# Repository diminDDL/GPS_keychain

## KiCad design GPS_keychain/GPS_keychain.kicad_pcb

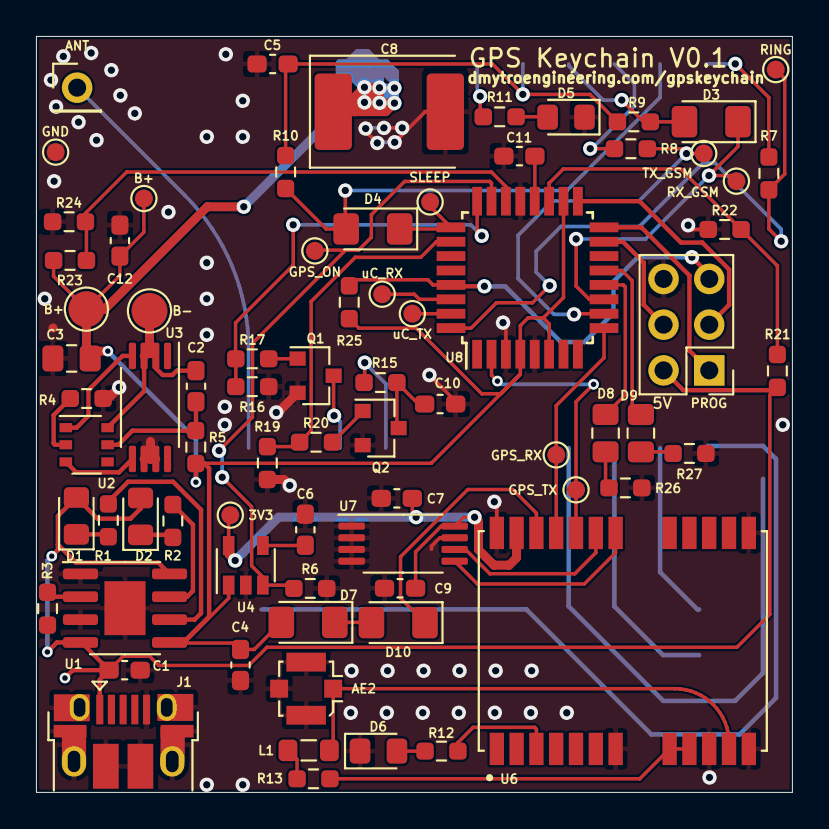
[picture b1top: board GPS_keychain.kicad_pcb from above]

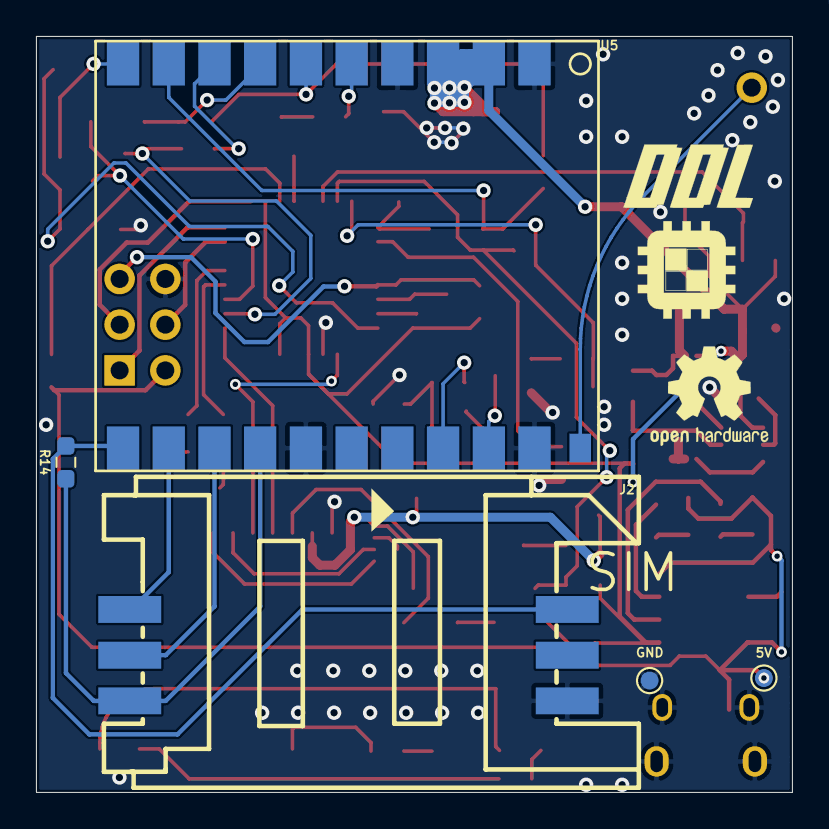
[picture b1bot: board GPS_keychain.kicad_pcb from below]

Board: 2 copper layers, 42.0 x 42.0 mm, 80 parts (5 on the bottom side), 63 nets.

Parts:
3V3: 3V3; TestPoint_Pad_D1.0mm
5V: 5V; TestPoint_Pad_D1.0mm
AE2: Antenna_Shield; U.FL_Molex_MCRF_73412-0110_Vertical
ANT: ANT; PinHeader_1x01_P2.54mm_Vertical
B+: BAT+; TestPoint_Pad_D1.0mm
B+#2: B+; TestPoint_Pad_D2.0mm
B-: B-; TestPoint_Pad_D2.0mm
C1, C2: 100n; C_0603_1608Metric_Pad1.08x0.95mm_HandSolder
C3: 10uF; C_0805_2012Metric_Pad1.18x1.45mm_HandSolder
C4, C7: 1uF; C_0603_1608Metric_Pad1.08x0.95mm_HandSolder
C5, C9, C10, C11, C12: 0.1uF; C_0603_1608Metric_Pad1.08x0.95mm_HandSolder
C6: 22nF; C_0603_1608Metric_Pad1.08x0.95mm_HandSolder
C8: 100uF; CP_EIA-7360-38_Kemet-E
D1: LED_G; LED_0805_2012Metric_Pad1.15x1.40mm_HandSolder
D2: LED_R; LED_0805_2012Metric_Pad1.15x1.40mm_HandSolder
D3, D4, D7, D10: S1MF; D_1206_3216Metric_Pad1.42x1.75mm_HandSolder
D5, D6: LED; LED_0805_2012Metric_Pad1.15x1.40mm_HandSolder
D8: LED_Y; C_0805_2012Metric_Pad1.18x1.45mm_HandSolder
D9: LED_B; C_0805_2012Metric_Pad1.18x1.45mm_HandSolder
GND: GND; TestPoint_Pad_D1.0mm
GND#2: GND; TestPoint_Pad_D1.0mm
GPS_ON: GPS_ON; TestPoint_Pad_D1.0mm
GPS_RX: RX_GPS; TestPoint_Pad_D1.0mm
GPS_TX: TX_GPS; TestPoint_Pad_D1.0mm
J1: USB_B_Micro; USB_Micro-B_Amphenol_10103594-0001LF_Horizontal
J2: SIM; SIM-SMD_XKSIM-011B-P6
L1: 27uH; L_0805_2012Metric_Pad1.05x1.20mm_HandSolder
PROG: AVR-ISP-6; PinHeader_2x03_P2.54mm_Vertical
Q1, Q2: BC846; SOT-23
R1, R2, R26, R27: 1K; R_0603_1608Metric_Pad0.98x0.95mm_HandSolder
R3: 1.2k; R_0603_1608Metric_Pad0.98x0.95mm_HandSolder
R4, R11, R12, R15: 1k; R_0603_1608Metric_Pad0.98x0.95mm_HandSolder
R5: 100; R_0603_1608Metric_Pad0.98x0.95mm_HandSolder
R6, R9, R10, R14, R17, R20, R21, R22, R25: 10k; R_0603_1608Metric_Pad0.98x0.95mm_HandSolder
R7, R8: 200; R_0603_1608Metric_Pad0.98x0.95mm_HandSolder
R13: 22R; R_0603_1608Metric_Pad0.98x0.95mm_HandSolder
R16, R19: 47k; R_0603_1608Metric_Pad0.98x0.95mm_HandSolder
R23: 10M; R_0603_1608Metric_Pad0.98x0.95mm_HandSolder
R24: 350k; R_0603_1608Metric_Pad0.98x0.95mm_HandSolder
RING: RG_GSM; TestPoint_Pad_D1.0mm
RX_GSM: RX_GSM; TestPoint_Pad_D1.0mm
SLEEP: SL_GSM; TestPoint_Pad_D1.0mm
TX_GSM: TX_GSM; TestPoint_Pad_D1.0mm
U1: TP4056; SOIC-8-1EP_3.9x4.9mm_P1.27mm_EP2.29x3mm
U2: DW01; TSOP-6_1.65x3.05mm_P0.95mm
U3: FS8205A; TSSOP-8_4.4x3mm_P0.65mm
U4: RT9193-33GB; SOT-23-5
U5: NeowayM590
U6: NEO-6M-GPS; XCVR_NEO-6M-GPS
U7: 24LC32; TSSOP-8_4.4x3mm_P0.65mm
U8: ATmega328P-AU; TQFP-32_7x7mm_P0.8mm
uC_RX: RX_uC; TestPoint_Pad_D1.0mm
uC_TX: TX_uC; TestPoint_Pad_D1.0mm

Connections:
+3V3: 3V3.1, C7.1, C9.2, U4.5, U6.23, U7.8
+5V: 5V.1, C1.1, D1.2, D2.2, J1.1, PROG.2, R21.2, U1.4, U1.8
+BATT: B+.1, B+#2.1, C3.1, C4.1, C8.1, C12.2, D7.2, R5.2, R23.2, R25.1, U1.5, U4.1, U5.2, U5.3, U8.4, U8.6, U8.18
/5V_sense: R21.1, R22.2, U8.19
/BAT_sense: R23.1, R24.2, U8.22
/GPS_ON: GPS_ON.1, R6.2, U4.3, U8.23
/GSM_EMOFF: R19.1, R20.1, U8.26
/GSM_EN: R16.1, R17.1, U8.24
/RING: R7.2, RING.1, U8.32
/RXD1: GPS_RX.1, U6.21, U8.9
/RXD2: D3.1, RX_GSM.1, U8.11
/RXD_uC: U8.30, uC_RX.1
/SLEEP: D4.1, SLEEP.1, U8.25
/TXD1: GPS_TX.1, U6.20, U8.2
/TXD2: R8.2, TX_GSM.1, U8.10
/TXD_uC: U8.31, uC_TX.1
GND: AE2.2, C1.2, C3.2, C4.2, C5.1, C6.2, C7.2, C8.2, C9.1, C10.2, C11.1, C12.1, D5.1, D6.1, GND.1, GND#2.1, J1.5, J1.6, J2.4, PROG.6, Q1.2, Q2.2, R3.1, R4.1, R6.1, R16.2, R19.2, R22.1, R24.1, R26.2, R27.1, U1.1, U1.3, U1.9, U3.6, U3.7, U4.2, U5.1, U5.4, U5.15, U5.20, U6.7, U6.10, U6.12, U6.13, U6.24, U7.1, U7.2, U7.3, U7.4, U7.7, U8.3, U8.5, U8.21
unnamed: ANT.1, U5.21
unnamed: AE2.1, L1.2, U6.11
unnamed: C2.1, R5.1, U2.5
unnamed: B-.1, C2.2, U2.6, U3.2, U3.3
unnamed: C5.2, R9.1, R10.1, U5.6
unnamed: C6.1, U4.4
unnamed: C10.1, Q2.3, R15.1
unnamed: C11.2, U8.20
unnamed: D1.1, R1.2
unnamed: D2.1, R2.2
unnamed: D3.2, R9.2, U5.7
unnamed: D4.2, R10.2, U5.9
unnamed: D5.2, R11.2
unnamed: D6.2, R12.1
unnamed: D8.1, R26.1
unnamed: D8.2, U8.12
unnamed: D9.1, R27.2
unnamed: D9.2, U8.13
unnamed: D10.1, U6.22
unnamed: D7.1, D10.2
unnamed: J2.1, R14.1, U5.14
unnamed: J2.2, U5.13
unnamed: J2.3, U5.12
unnamed: J2.6, R14.2, U5.11
unnamed: PROG.1, U8.16
unnamed: PROG.3, U8.17
unnamed: PROG.4, U8.15
unnamed: PROG.5, R25.2, U8.29
unnamed: L1.1, R13.1
unnamed: Q1.1, R17.2
unnamed: Q1.3, U5.19
unnamed: Q2.1, R20.2
unnamed: R1.1, U1.6
unnamed: R2.1, U1.7
unnamed: R3.2, U1.2
unnamed: R4.2, U2.2
unnamed: R7.1, U5.10
unnamed: R8.1, U5.8
unnamed: R11.1, U5.5
unnamed: R12.2, U6.3
unnamed: R13.2, U6.8, U6.9
unnamed: R15.2, U5.18
unnamed: U2.1, U3.4
unnamed: U2.3, U3.5
unnamed: U6.18, U7.5
unnamed: U6.19, U7.6

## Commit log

2021-10-25 Upload alpha hardware
